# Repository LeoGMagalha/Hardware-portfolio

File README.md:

# Portfólio de Hardware

Este repositório contém uma coleção de projetos de hardware, demonstrando habilidades e experiências em design e implementação de sistemas eletrônicos. Cada projeto é organizado em sua própria pasta, com detalhes adicionais disponíveis em seus respectivos READMEs.

## Projetos

### 1. Pedido casamento

O primeiro projeto consiste em um painel de LEDs controlado por circuitos integrados e portas lógicas para exibir a mensagem "Casa comigo?". Utilizando a lógica digital, os LEDs são manipulados para formar as letras da mensagem de forma sincronizada e brilhante. Este dispositivo não apenas demonstra habilidades em design de hardware e eletrônica digital, mas também adiciona um toque personalizado e memorável a um pedido de casamento. Para mais detalhes, consulte o README na pasta `pedido_casamento_smd`.

### 2. Fonte de bancada linear

Este projeto apresenta uma fonte de bancada linear de 48W com saídas de tensão ajustáveis positiva e negativa, oferecendo uma corrente máxima de 2A a 24V. Implementado com amplificadores operacionais, um Arduino e um LCD cristal, este dispositivo proporciona precisão e controle sobre a saída de energia. Além disso, inclui recursos de proteção com limitação de corrente, garantindo a segurança do equipamento conectado. Com a adição de voltímetro e amperímetro, os usuários podem monitorar facilmente a tensão e a corrente de saída, tornando-o uma solução versátil e confiável para diversas aplicações de eletrônica. Para mais informações, consulte o README na pasta `Fonte_bancada_linear_48W`.

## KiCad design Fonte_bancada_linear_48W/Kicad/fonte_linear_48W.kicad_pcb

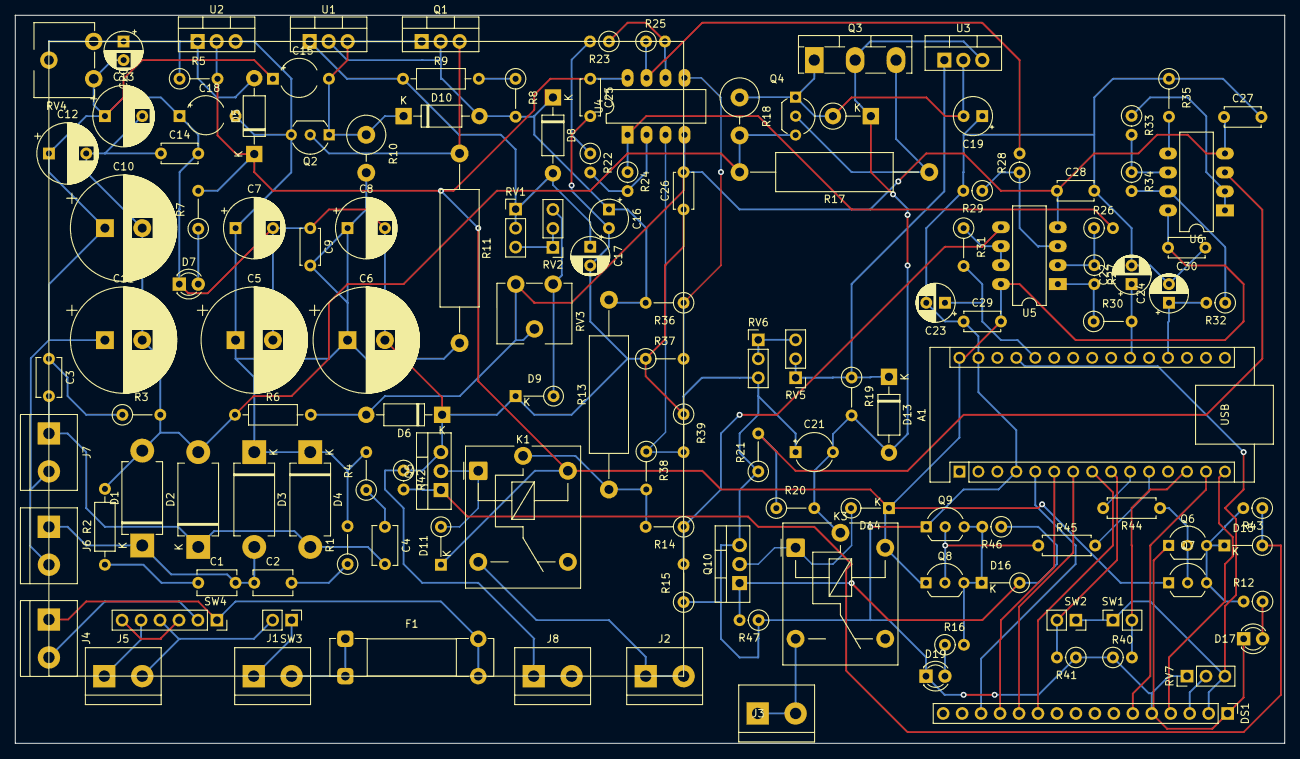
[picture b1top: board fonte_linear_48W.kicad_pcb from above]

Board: 2 copper layers, 170.0 x 97.5 mm, 135 parts (0 on the bottom side), 77 nets.

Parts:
A1: Arduino_Nano_v3.x; Arduino_Nano
C1, C2, C3, C4: 100nF; C_Disc_D5.1mm_W3.2mm_P5.00mm
C5, C6, C10, C11: 1000uF; CP_Radial_D14.0mm_P5.00mm
C7, C8, C12, C13: 100uF; CP_Radial_D8.0mm_P5.00mm
C9, C14: 100nF; C_Disc_D4.7mm_W2.5mm_P5.00mm
C15, C18: 0.1uF; CP_Radial_Tantal_D5.0mm_P7.50mm
C16, C19: 1uF; CP_Radial_Tantal_D5.0mm_P2.50mm
C17, C20, C22, C23, C24: 10uF; CP_Radial_D5.0mm_P2.50mm
C21: 1uF; CP_Radial_Tantal_D5.0mm_P5.00mm
C25, C26, C27, C28, C29, C30: 10nF; C_Disc_D4.7mm_W2.5mm_P5.00mm
D1, D2, D3, D4: 1N5408; D_DO-201AD_P12.70mm_Horizontal
D5, D8, D10, D13: 1N4007; D_DO-41_SOD81_P10.16mm_Horizontal
D6: 1N4740A; D_DO-41_SOD81_P10.16mm_Horizontal
D7, D17, D19: LED; LED_D3.0mm
D9, D11, D14, D15, D16: 1N4148; D_DO-35_SOD27_P5.08mm_Vertical_KathodeUp
D12: 1N4007; D_DO-41_SOD81_P5.08mm_Vertical_KathodeUp
DS1: WC1602A; PinHeader_1x16_P2.54mm_Vertical
F1: 2.5A; Fuseholder_Clip-5x20mm_Bel_FC-203-22_Lateral_P17.80x5.00mm_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
J1: AC_IN; TerminalBlock_bornier-2_P5.08mm
J2: Vout+; TerminalBlock_bornier-2_P5.08mm
J3: Vout-; TerminalBlock_bornier-2_P5.08mm
J4: TrVmAm; TerminalBlock_bornier-2_P5.08mm
J5: TrPTVD; TerminalBlock_bornier-2_P5.08mm
J6: +24VGND; TerminalBlock_bornier-2_P5.08mm
J7: GND+24V; TerminalBlock_bornier-2_P5.08mm
J8: GNDout; TerminalBlock_bornier-2_P5.08mm
K1, K3: Relay_SPDT; Relay_SPDT_Finder_36.11
Q1: TIP42C; TO-220-3_Vertical
Q2, Q6, Q9: BC327; TO-92_Inline_Wide
Q3: TIP3055; TO-218-3_Vertical
Q4, Q7, Q8: BC337; TO-92_Inline_Wide
Q5, Q10: IRF640N; TO-220-3_Vertical
R1, R3, R4: 1; R_Axial_DIN0207_L6.3mm_D2.5mm_P5.08mm_Vertical
R2: 1; R_Axial_DIN0207_L6.3mm_D2.5mm_P10.16mm_Horizontal
R5: 1k; R_Axial_DIN0207_L6.3mm_D2.5mm_P5.08mm_Vertical
R6: 1k; R_Axial_DIN0207_L6.3mm_D2.5mm_P10.16mm_Horizontal
R7, R19: 680; R_Axial_DIN0207_L6.3mm_D2.5mm_P5.08mm_Vertical
R8: 510; R_Axial_DIN0207_L6.3mm_D2.5mm_P5.08mm_Vertical
R9: 22; R_Axial_DIN0207_L6.3mm_D2.5mm_P10.16mm_Horizontal
R10, R18: 10 1W; R_Axial_DIN0516_L15.5mm_D5.0mm_P5.08mm_Vertical
R11, R17: 0.68 5W; R_Axial_DIN0516_L15.5mm_D5.0mm_P25.40mm_Horizontal
R12, R16: 1k; R_Axial_DIN0207_L6.3mm_D2.5mm_P2.54mm_Vertical
R13: 0.47 5W; R_Axial_DIN0516_L15.5mm_D5.0mm_P25.40mm_Horizontal
R14, R20: 20k; R_Axial_DIN0207_L6.3mm_D2.5mm_P5.08mm_Vertical
R15, R21: 5k1; R_Axial_DIN0207_L6.3mm_D2.5mm_P5.08mm_Vertical
R22, R23, R24, R25: 4k7; R_Axial_DIN0207_L6.3mm_D2.5mm_P2.54mm_Vertical
R26, R28: 470; R_Axial_DIN0207_L6.3mm_D2.5mm_P2.54mm_Vertical
R27, R29, R32: 6k8; R_Axial_DIN0207_L6.3mm_D2.5mm_P2.54mm_Vertical
R30, R31, R37, R39: 6k8; R_Axial_DIN0207_L6.3mm_D2.5mm_P5.08mm_Vertical
R33, R34: 100k; R_Axial_DIN0207_L6.3mm_D2.5mm_P2.54mm_Vertical
R35: 51k; R_Axial_DIN0207_L6.3mm_D2.5mm_P5.08mm_Vertical
R36, R38: 47k; R_Axial_DIN0207_L6.3mm_D2.5mm_P5.08mm_Vertical
R40, R41: 5k1; R_Axial_DIN0207_L6.3mm_D2.5mm_P2.54mm_Vertical
R42, R47: 20k; R_Axial_DIN0207_L6.3mm_D2.5mm_P2.54mm_Vertical
R43, R46: 10; R_Axial_DIN0207_L6.3mm_D2.5mm_P2.54mm_Vertical
R44, R45: 330; R_Axial_DIN0207_L6.3mm_D2.5mm_P7.62mm_Horizontal
RV1, RV5: 1k; PinHeader_1x03_P2.54mm_Vertical
RV2, RV6, RV7: 10k; PinHeader_1x03_P2.54mm_Vertical
RV3, RV4: 10k; Potentiometer_ACP_CA9-V6_Vertical
SW1: V-ON/OFF; PinSocket_1x02_P2.54mm_Vertical
SW2: V+ON/OFF; PinSocket_1x02_P2.54mm_Vertical
SW3: ON/OFFG; PinHeader_1x02_P2.54mm_Vertical
SW4: 110/220V; PinSocket_1x06_P2.54mm_Vertical
U1, U2: LM317_TO-220; TO-220-3_Vertical
U3: LM337_TO220; TO-220-3_Vertical
U4, U5, U6: LM358; CERDIP-8_W7.62mm_SideBrazed_LongPads

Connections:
/+5V: A1.27 (+5V), DS1.2 (VDD), RV7.3, SW1.1 (B), SW2.1 (B)
/+12V: A1.30 (VIN), C25.1, C29.2, C30.2, D5.1 (K), D11.1 (K), D14.1 (K), K1.A2, K3.A2, Q7.1 (C), Q8.1 (C), R5.2, R7.2, U2.2 (VO), U4.8 (V+), U5.8 (V+), U6.8 (V+)
/+33V: C5.1, C6.1, C7.1, C8.1, C9.2, C18.2, D3.1 (K), D4.1 (K), Q2.3 (E), R1.2, R4.2, R10.2, R11.2, U2.3 (VI)
/+VoutAD: A1.26 (A7), C23.1, R31.2
/-10V: C26.2, C27.1, C28.1, D6.2 (A), R6.2, RV3.1, RV3.2, U4.4 (V-), U5.4 (V-), U6.4 (V-)
/-33V: C10.2, C11.2, C12.2, C13.2, C14.1, D1.2 (A), D2.2 (A), Q4.3 (E), R2.2, R3.2, R6.1, R17.2, R18.2
/-VoutAD: A1.19 (A0), C24.1, R32.2
/BOBv+: D11.2 (A), K1.A1, Q5.2 (D)
/BOBv-: D14.2 (A), K3.A1, Q10.2 (D)
/I_meas+: R36.1, R37.2, U4.5 (+)
/I_meas-: R38.1, R39.2, U4.3 (+)
/IoutAD: A1.21 (A2), C22.1, R30.2
/NAN02: A1.5 (D2), DS1.14 (D7)
/NAN03: A1.6 (D3), DS1.13 (D6)
/NAN04: A1.7 (D4), DS1.12 (D5)
/NAN05: A1.8 (D5), DS1.11 (D4)
/NAN11: A1.14 (D11), DS1.6 (E)
/NAN12: A1.15 (D12), DS1.4 (RS)
/NMOSV+: A1.10 (D7), R44.2
/NMOSV-: A1.11 (D8), R45.2
/Vout+_meas: R14.1, R15.2, U5.5 (+)
/Vout-_meas: R20.1, R21.2, U6.3 (+)
GND: A1.4 (GND), A1.29 (GND), C5.2, C6.2, C7.2, C8.2, C9.1, C10.1, C11.1, C12.1, C13.1, C14.2, C15.1, C16.2, C17.2, C18.1, C19.1, C20.2, C21.1, C22.2, C23.2, C24.2, C25.2, C26.1, C27.2, C28.2, C29.1, C30.1, D6.1 (K), D7.1 (K), D9.1 (K), D17.1 (K), D19.1 (K), DS1.1 (VSS), DS1.5 (R/W), J6.2, J7.2, J8.1, J8.2, Q5.3 (S), Q6.1 (C), Q9.1 (C), Q10.3 (S), R15.1, R21.1, R29.2, R35.1, R37.1, R39.1, R40.1, R41.1, R42.1, R47.1, RV4.3, RV6.3, RV7.1
unnamed: A1.9 (D6), R41.2, SW2.2 (A)
unnamed: A1.13 (D10), R40.2, SW1.2 (A)
unnamed: C1.1, R2.1
unnamed: C2.2, R1.1
unnamed: C3.1, R3.1
unnamed: C4.1, R4.1
unnamed: C1.2, C2.1, D1.1 (K), D3.2 (A), J6.1
unnamed: C3.2, C4.2, D2.1 (K), D4.2 (A), J7.1
unnamed: C20.1, D5.2 (A), R5.1, RV4.1, RV4.2, U2.1 (ADJ)
unnamed: D7.2 (A), R7.1
unnamed: C17.1, D8.2 (A), R9.1, RV1.1, RV1.2, U1.1 (ADJ)
unnamed: D9.2 (A), RV2.3, RV3.3
unnamed: C16.1, D8.1 (K), D10.2 (A), Q1.2 (C), R8.2, R13.2, R36.2, U1.2 (VO)
unnamed: C15.2, D10.1 (K), Q1.1 (B), Q2.1 (C), R10.1, U1.3 (VI)
unnamed: C19.2, D12.2 (A), Q3.1 (B), Q4.1 (C), R18.1, U3.2 (VI)
unnamed: C21.2, D12.1 (K), D13.2 (A), K3.11, Q3.2 (C), R19.2, R20.2, U3.3 (VO)
unnamed: D13.1 (K), R19.1, RV5.1, RV5.2, U3.1 (ADJ)
unnamed: D15.2 (A), Q5.1 (G), R42.2, R43.1
unnamed: D15.1 (K), Q6.3 (E), Q7.3 (E), R12.2, R43.2
unnamed: D16.2 (A), Q10.1 (G), R46.1, R47.2
unnamed: D16.1 (K), Q8.3 (E), Q9.3 (E), R16.2, R46.2
unnamed: D17.2 (A), R12.1
unnamed: D19.2 (A), R16.1
unnamed: DS1.3 (VO), RV7.2
unnamed: J1.1, SW3.1 (A)
unnamed: F1.1, J1.2
unnamed: J2.1, J2.2, K1.14
unnamed: J3.1, J3.2, K3.14
unnamed: F1.2, J4.1, SW4.1 (A)
unnamed: J4.2, SW4.2 (B)
unnamed: J5.1, SW4.5 (B)
unnamed: J5.2, SW3.2 (B), SW4.4 (A)
unnamed: K1.11, R13.1, R14.2, R38.2
unnamed: Q1.3 (E), Q2.2 (B), R11.1
unnamed: Q3.3 (E), Q4.2 (B), R17.1
unnamed: Q6.2 (B), Q7.2 (B), R44.1
unnamed: Q8.2 (B), Q9.2 (B), R45.1
unnamed: R8.1, R9.2
unnamed: R22.1, R23.2
unnamed: R24.1, R26.2, U4.1
unnamed: R25.1, R28.2, U4.7
unnamed: R27.2, R30.1, U5.1
unnamed: R32.1, R34.2, U6.7
unnamed: RV1.3, RV2.1, RV2.2
unnamed: RV5.3, RV6.1, RV6.2
unnamed: SW4.3 (C), SW4.6 (C)
unnamed: R22.2, R24.2, U4.2 (-)
unnamed: R23.1, R25.2, U4.6 (-)
unnamed: R28.1, R29.1, U5.3 (+)
unnamed: R26.1, R27.1, U5.2 (-)
unnamed: R31.1, U5.6 (-), U5.7
unnamed: R33.1, U6.1, U6.2 (-)
unnamed: R35.2, U6.5 (+)
unnamed: R33.2, R34.1, U6.6 (-)

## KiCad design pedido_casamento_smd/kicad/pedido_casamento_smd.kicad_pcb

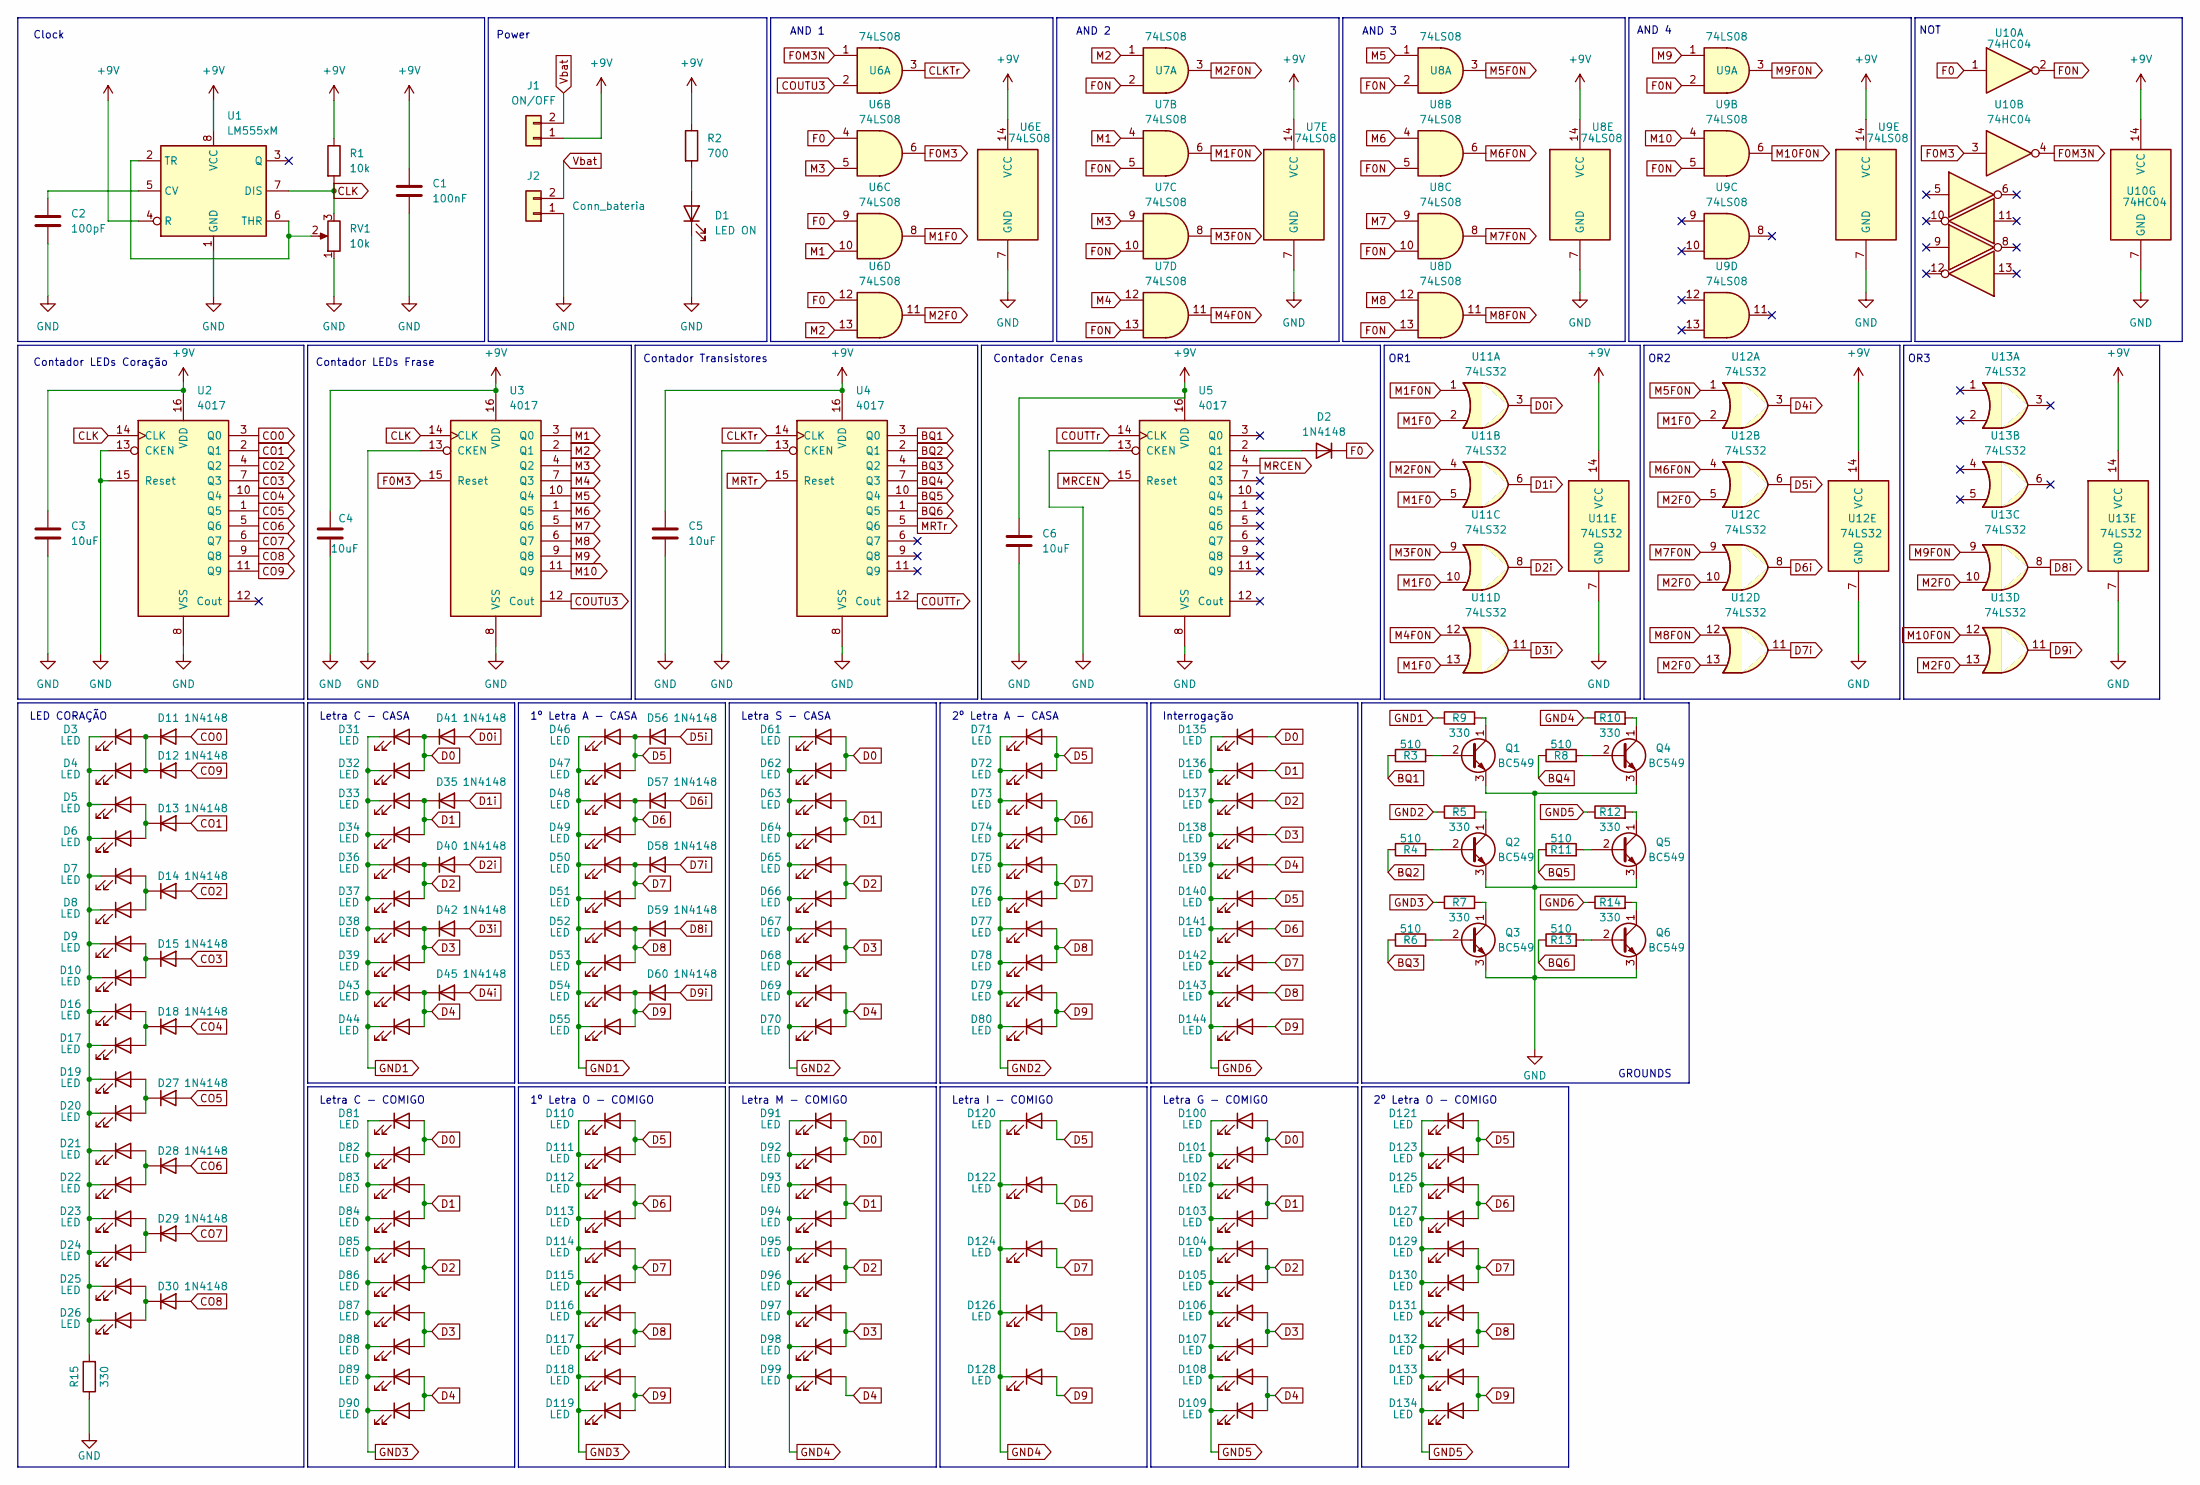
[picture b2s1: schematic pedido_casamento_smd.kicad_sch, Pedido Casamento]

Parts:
C1: 100nF; C_0805_2012Metric
C2: 100pF; C_0201_0603Metric_Pad0.64x0.40mm_HandSolder
C3, C4, C5, C6: 10uF; C_Elec_6.3x7.7
D1: LED ON; LED_1206_3216Metric
D2, D11, D12, D13, D14, D15, D18, D27, D28, D29, D30, D35, D40, D41, D42, D45, D56, D57, D58, D59, D60: 1N4148; D_0805_2012Metric_Pad1.15x1.40mm_HandSolder
D3, D4, D5, D6, D7, D8, D9, D10, D16, D17, D19, D20, D21, D22, D23, D24, D25, D26, D31, D32, D33, D34, D36, D37, D38, D39, D43, D44, D46, D47, D48, D49, D50, D51, D52, D53, D54, D55, D61, D62, D63, D64, D65, D66, D67, D68, D69, D70, D71, D72, D73, D74, D75, D76, D77, D78, D79, D80, D81, D82, D83, D84, D85, D86, D87, D88, D89, D90, D91, D92, D93, D94, D95, D96, D97, D98, D99, D100, D101, D102, D103, D104, D105, D106, D107, D108, D109, D110, D111, D112, D113, D114, D115, D116, D117, D118, D119, D120, D121, D122, D123, D124, D125, D126, D127, D128, D129, D130, D131, D132, D133, D134, D135, D136, D137, D138, D139, D140, D141, D142, D143, D144: LED; LED_1206_3216Metric
J1: ON/OFF; PinHeader_1x02_P2.54mm_Vertical
J2: Conn_bateria; PinHeader_1x02_P2.54mm_Vertical
Q1, Q2, Q3, Q4, Q5, Q6: BC549; TO-92_Inline
R1: 10k; R_0805_2012Metric_Pad1.20x1.40mm_HandSolder
R2: 700; R_0805_2012Metric_Pad1.20x1.40mm_HandSolder
R3, R4, R6, R8, R11, R13: 510; R_0805_2012Metric_Pad1.20x1.40mm_HandSolder
R5, R7, R9, R10, R12, R14, R15: 330; R_0805_2012Metric_Pad1.20x1.40mm_HandSolder
RV1: 10k; Potentiometer_ACP_CA9-V10_Vertical
U1: LM555xM; SOIC-8_3.9x4.9mm_P1.27mm
U2, U3, U4, U5: 4017; TSSOP-16_4.4x5mm_P0.65mm
U6, U7, U8, U9: 74LS08; SOIC-14_3.9x8.7mm_P1.27mm
U10: 74HC04; SOIC-14_3.9x8.7mm_P1.27mm
U11, U12, U13: 74LS32; SOIC-14_3.9x8.7mm_P1.27mm

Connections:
+9V: C1.1, C3.1, C4.1, C5.1, C6.1, J1.1, R1.1, R2.1, U1.4 (R), U1.8 (VCC), U2.16 (VDD), U3.16 (VDD), U4.16 (VDD), U5.16 (VDD), U6.14 (VCC), U7.14 (VCC), U8.14 (VCC), U9.14 (VCC), U10.14 (VCC), U11.14 (VCC), U12.14 (VCC), U13.14 (VCC)
BQ1: R3.1, U4.3 (Q0)
BQ2: R4.1, U4.2 (Q1)
BQ3: R6.1, U4.4 (Q2)
BQ4: R8.1, U4.7 (Q3)
BQ5: R11.1, U4.10 (Q4)
BQ6: R13.1, U4.1 (Q5)
CLK: R1.2, RV1.3, U1.7 (DIS), U2.14 (CLK), U3.14 (CLK)
CLKTr: U4.14 (CLK), U6.3
CO0: D11.2 (A), U2.3 (Q0)
CO1: D13.2 (A), U2.2 (Q1)
CO2: D14.2 (A), U2.4 (Q2)
CO3: D15.2 (A), U2.7 (Q3)
CO4: D18.2 (A), U2.10 (Q4)
CO5: D27.2 (A), U2.1 (Q5)
CO6: D28.2 (A), U2.5 (Q6)
CO7: D29.2 (A), U2.6 (Q7)
CO8: D30.2 (A), U2.9 (Q8)
CO9: D12.2 (A), U2.11 (Q9)
COUTTr: U4.12 (Cout), U5.14 (CLK)
COUTU3: U3.12 (Cout), U6.2
D0: D31.2 (A), D32.2 (A), D41.1 (K), D61.2 (A), D62.2 (A), D81.2 (A), D82.2 (A), D91.2 (A), D92.2 (A), D100.2 (A), D101.2 (A), D135.2 (A)
D0i: D41.2 (A), U11.3
D1: D33.2 (A), D34.2 (A), D35.1 (K), D63.2 (A), D64.2 (A), D83.2 (A), D84.2 (A), D93.2 (A), D94.2 (A), D102.2 (A), D103.2 (A), D136.2 (A)
D1i: D35.2 (A), U11.6
D2: D36.2 (A), D37.2 (A), D40.1 (K), D65.2 (A), D66.2 (A), D85.2 (A), D86.2 (A), D95.2 (A), D96.2 (A), D104.2 (A), D105.2 (A), D137.2 (A)
D2i: D40.2 (A), U11.8
D3: D38.2 (A), D39.2 (A), D42.1 (K), D67.2 (A), D68.2 (A), D87.2 (A), D88.2 (A), D97.2 (A), D98.2 (A), D106.2 (A), D107.2 (A), D138.2 (A)
D3i: D42.2 (A), U11.11
D4: D43.2 (A), D44.2 (A), D45.1 (K), D69.2 (A), D70.2 (A), D89.2 (A), D90.2 (A), D99.2 (A), D108.2 (A), D109.2 (A), D139.2 (A)
D4i: D45.2 (A), U12.3
D5: D46.2 (A), D47.2 (A), D56.1 (K), D71.2 (A), D72.2 (A), D110.2 (A), D111.2 (A), D120.2 (A), D121.2 (A), D123.2 (A), D140.2 (A)
D5i: D56.2 (A), U12.6
D6: D48.2 (A), D49.2 (A), D57.1 (K), D73.2 (A), D74.2 (A), D112.2 (A), D113.2 (A), D122.2 (A), D125.2 (A), D127.2 (A), D141.2 (A)
D6i: D57.2 (A), U12.8
D7: D50.2 (A), D51.2 (A), D58.1 (K), D75.2 (A), D76.2 (A), D114.2 (A), D115.2 (A), D124.2 (A), D129.2 (A), D130.2 (A), D142.2 (A)
D7i: D58.2 (A), U12.11
D8: D52.2 (A), D53.2 (A), D59.1 (K), D77.2 (A), D78.2 (A), D116.2 (A), D117.2 (A), D126.2 (A), D131.2 (A), D132.2 (A), D143.2 (A)
D8i: D59.2 (A), U13.8
D9: D54.2 (A), D55.2 (A), D60.1 (K), D79.2 (A), D80.2 (A), D118.2 (A), D119.2 (A), D128.2 (A), D133.2 (A), D134.2 (A), D144.2 (A)
D9i: D60.2 (A), U13.11
F0: D2.1 (K), U6.4, U6.9, U6.12, U10.1
F0M3: U3.15 (Reset), U6.6, U10.3
F0M3N: U6.1, U10.4
F0N: U7.2, U7.5, U7.10, U7.13, U8.2, U8.5, U8.10, U8.13, U9.2, U9.5, U10.2
GND: C1.2, C2.2, C3.2, C4.2, C5.2, C6.2, D1.1 (K), J2.1, Q1.3 (E), Q2.3 (E), Q3.3 (E), Q4.3 (E), Q5.3 (E), Q6.3 (E), R15.1, RV1.1, U1.1 (GND), U2.8 (VSS), U2.13 (CKEN), U2.15 (Reset), U3.8 (VSS), U3.13 (CKEN), U4.8 (VSS), U4.13 (CKEN), U5.8 (VSS), U5.13 (CKEN), U6.7 (GND), U7.7 (GND), U8.7 (GND), U9.7 (GND), U10.7 (GND), U11.7 (GND), U12.7 (GND), U13.7 (GND)
GND1: D31.1 (K), D32.1 (K), D33.1 (K), D34.1 (K), D36.1 (K), D37.1 (K), D38.1 (K), D39.1 (K), D43.1 (K), D44.1 (K), D46.1 (K), D47.1 (K), D48.1 (K), D49.1 (K), D50.1 (K), D51.1 (K), D52.1 (K), D53.1 (K), D54.1 (K), D55.1 (K), R9.1
GND2: D61.1 (K), D62.1 (K), D63.1 (K), D64.1 (K), D65.1 (K), D66.1 (K), D67.1 (K), D68.1 (K), D69.1 (K), D70.1 (K), D71.1 (K), D72.1 (K), D73.1 (K), D74.1 (K), D75.1 (K), D76.1 (K), D77.1 (K), D78.1 (K), D79.1 (K), D80.1 (K), R5.1
GND3: D81.1 (K), D82.1 (K), D83.1 (K), D84.1 (K), D85.1 (K), D86.1 (K), D87.1 (K), D88.1 (K), D89.1 (K), D90.1 (K), D110.1 (K), D111.1 (K), D112.1 (K), D113.1 (K), D114.1 (K), D115.1 (K), D116.1 (K), D117.1 (K), D118.1 (K), D119.1 (K), R7.1
GND4: D91.1 (K), D92.1 (K), D93.1 (K), D94.1 (K), D95.1 (K), D96.1 (K), D97.1 (K), D98.1 (K), D99.1 (K), D120.1 (K), D122.1 (K), D124.1 (K), D126.1 (K), D128.1 (K), R10.1
GND5: D100.1 (K), D101.1 (K), D102.1 (K), D103.1 (K), D104.1 (K), D105.1 (K), D106.1 (K), D107.1 (K), D108.1 (K), D109.1 (K), D121.1 (K), D123.1 (K), D125.1 (K), D127.1 (K), D129.1 (K), D130.1 (K), D131.1 (K), D132.1 (K), D133.1 (K), D134.1 (K), R12.1
GND6: D135.1 (K), D136.1 (K), D137.1 (K), D138.1 (K), D139.1 (K), D140.1 (K), D141.1 (K), D142.1 (K), D143.1 (K), D144.1 (K), R14.1
M1: U3.3 (Q0), U6.10, U7.4
M1F0: U6.8, U11.2, U11.5, U11.10, U11.13, U12.2
M1F0N: U7.6, U11.1
M2: U3.2 (Q1), U6.13, U7.1
M2F0: U6.11, U12.5, U12.10, U12.13, U13.10, U13.13
M2F0N: U7.3, U11.4
M3: U3.4 (Q2), U6.5, U7.9
M3F0N: U7.8, U11.9
M4: U3.7 (Q3), U7.12
M4F0N: U7.11, U11.12
M5: U3.10 (Q4), U8.1
M5F0N: U8.3, U12.1
M6: U3.1 (Q5), U8.4
M6F0N: U8.6, U12.4
M7: U3.5 (Q6), U8.9
M7F0N: U8.8, U12.9
M8: U3.6 (Q7), U8.12
M8F0N: U8.11, U12.12
M9: U3.9 (Q8), U9.1
M9F0N: U9.3, U13.9
M10: U3.11 (Q9), U9.4
M10F0N: U9.6, U13.12
MRCEN: U5.4 (Q2), U5.15 (Reset)
MRTr: U4.5 (Q6), U4.15 (Reset)
unnamed: D1.2 (A), R2.2
unnamed: D2.2 (A), U5.2 (Q1)
unnamed: D9.2 (A), D10.2 (A), D15.1 (K)
unnamed 79: D3.1 (K), D4.1 (K), D5.1 (K), D6.1 (K), D7.1 (K), D8.1 (K), D9.1 (K), D10.1 (K), D16.1 (K), D17.1 (K), D19.1 (K), D20.1 (K), D21.1 (K), D22.1 (K), D23.1 (K), D24.1 (K), D25.1 (K), D26.1 (K), R15.2; also elsewhere on the board
unnamed: D3.2 (A), D4.2 (A), D11.1 (K), D12.1 (K)
unnamed: D5.2 (A), D6.2 (A), D13.1 (K)
unnamed: D7.2 (A), D8.2 (A), D14.1 (K)
unnamed: D16.2 (A), D17.2 (A), D18.1 (K)
unnamed 84: D19.2 (A), D20.2 (A), D27.1 (K); also elsewhere on the board
unnamed: D21.2 (A), D22.2 (A), D28.1 (K)
unnamed: D23.2 (A), D24.2 (A), D29.1 (K)
unnamed: D25.2 (A), D26.2 (A), D30.1 (K)
unnamed: Q1.2 (B), R3.2
unnamed: Q1.1 (C), R9.2
unnamed: Q2.2 (B), R4.2
unnamed: Q2.1 (C), R5.2
unnamed: Q3.2 (B), R6.2
unnamed: Q3.1 (C), R7.2
unnamed: Q4.2 (B), R8.2
unnamed: Q4.1 (C), R10.2
unnamed: Q5.2 (B), R11.2
unnamed: Q5.1 (C), R12.2
unnamed: Q6.2 (B), R13.2
unnamed: Q6.1 (C), R14.2
unnamed: C2.1, U1.5 (CV)
unnamed: RV1.2, U1.2 (TR), U1.6 (THR)
Vbat: J1.2, J2.2

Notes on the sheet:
Letra S - CASA
GROUNDS
Contador LEDs Frase
AND 2
AND 4
Letra M - COMIGO
Letra G - COMIGO
Letra C - CASA
Contador Transistores
OR1
NOT
Power
Clock
AND 3
LED CORAÇÃO
AND 1
Contador Cenas
Contador LEDs Coração
OR3
Letra C - COMIGO
2º Letra O - COMIGO
Interrogação
2º Letra A - CASA
Letra I - COMIGO
1º Letra O - COMIGO
OR2
1º Letra A - CASA

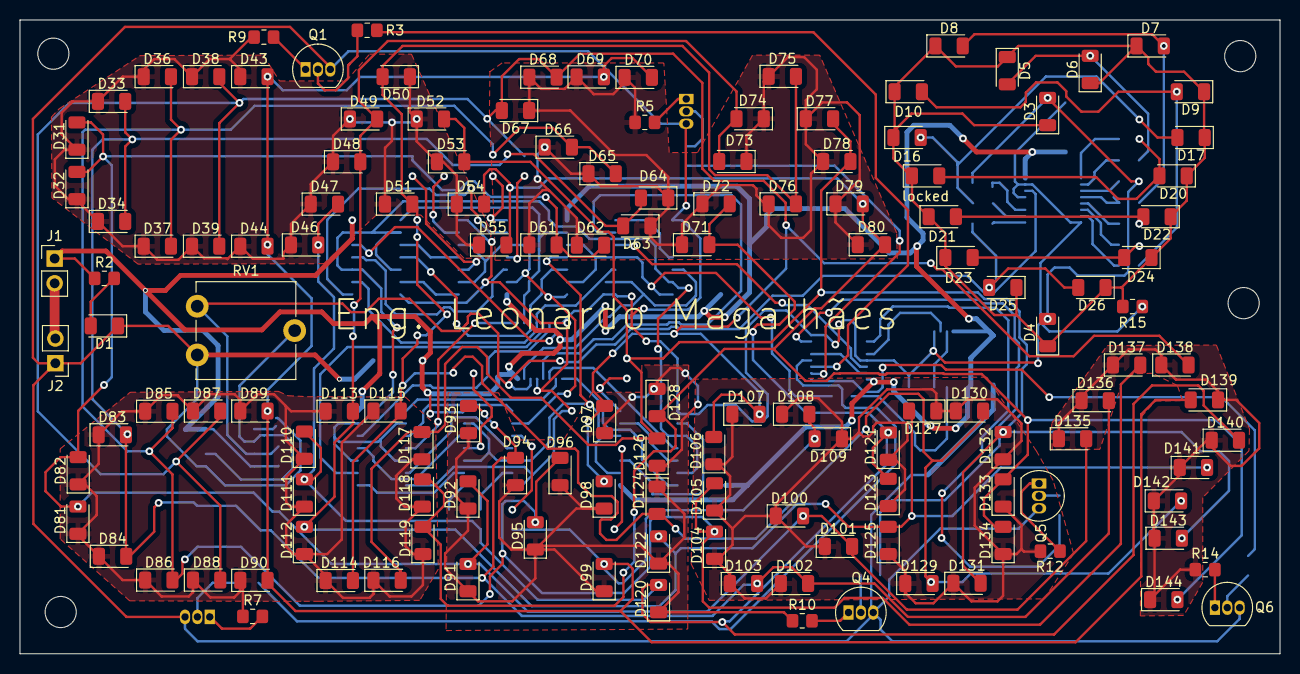
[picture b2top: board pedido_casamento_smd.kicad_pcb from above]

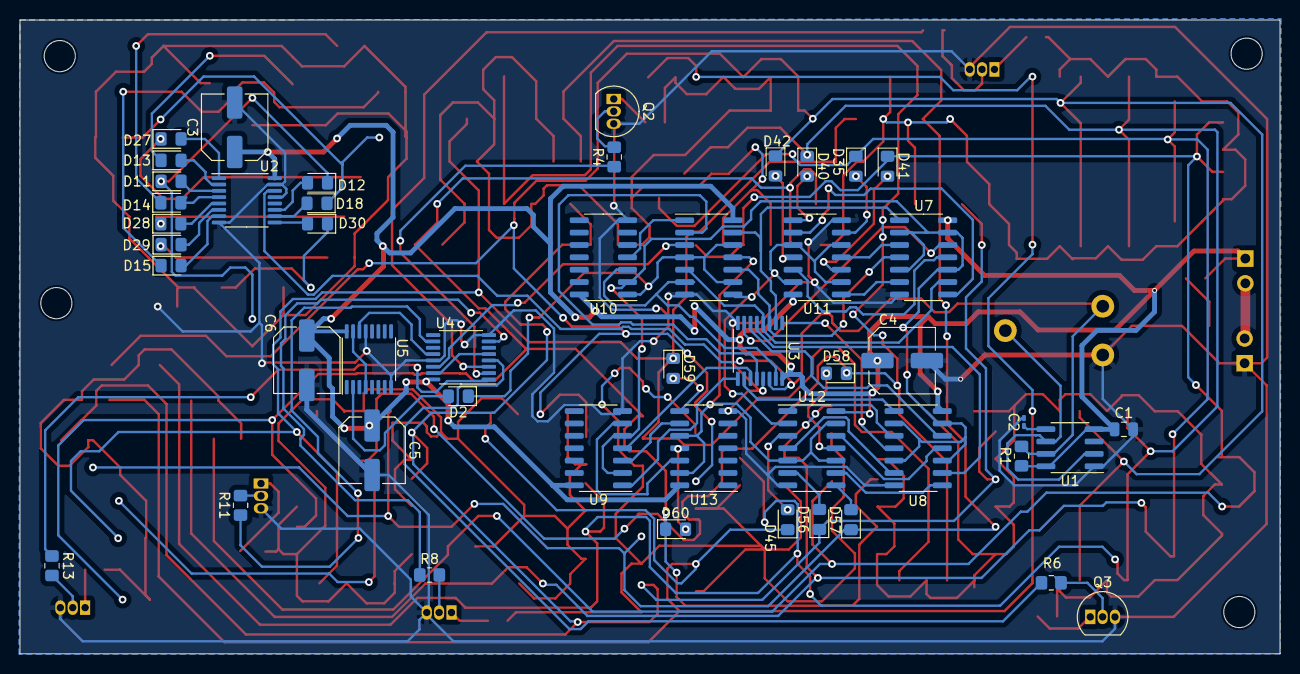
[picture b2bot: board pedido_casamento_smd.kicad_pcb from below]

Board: 2 copper layers, 129.3 x 65.0 mm, 187 parts (48 on the bottom side), 103 nets.

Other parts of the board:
locked: LED; LED_1206_3216Metric

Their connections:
unnamed 79: locked.1 (K); also elsewhere on the board
unnamed 84: locked.2 (A); also elsewhere on the board

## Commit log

2024-02-14 primeiro comit
2024-02-15 alterando descricao
2024-02-15 add esquematico em pdf
2024-02-15 atualiza descricao
2024-06-01 projeto fonte de bancada linear 48W
2024-06-01 add readme
2024-06-01 update repo
2024-06-01 fix descricao
2024-06-01 fix gitignore
2024-06-01 remove backups
